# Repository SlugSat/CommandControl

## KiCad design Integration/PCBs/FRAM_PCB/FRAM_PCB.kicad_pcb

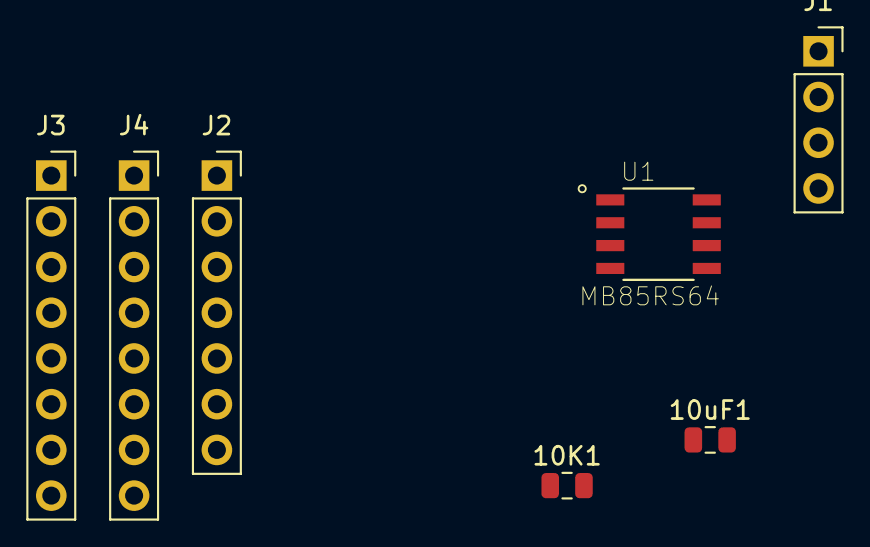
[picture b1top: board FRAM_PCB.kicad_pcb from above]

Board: 2 copper layers, 7 parts (0 on the bottom side), 12 nets, no tracks yet.

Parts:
10K1: R; R_0805_2012Metric
10uF1: C; C_0805_2012Metric
J1: Conn_01x04_Male; PinSocket_1x04_P2.54mm_Vertical
J2: Conn_01x07_Male; PinSocket_1x07_P2.54mm_Vertical
J3, J4: Conn_01x08_Female; PinSocket_1x08_P2.54mm_Vertical
U1: MB85RS64; SOIC127P600X175-8N

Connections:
+5V: 10K1.2, 10uF1.1, J2.6, U1.8
GND: 10uF1.2, J2.7, U1.4
unnamed: 10K1.1, U1.7
unnamed: J1.1, J3.1, J4.1, J4.8
unnamed: J1.2, J3.2, J3.6, J3.7, J3.8, J4.2, J4.6, J4.7
unnamed: J1.3, J3.4, J4.4
unnamed: J1.4, J3.5, J4.5
unnamed: J2.1, U1.2
unnamed: J2.2, U1.5
unnamed: J2.3, U1.6
unnamed: J2.4, U1.3
unnamed: J2.5, U1.1

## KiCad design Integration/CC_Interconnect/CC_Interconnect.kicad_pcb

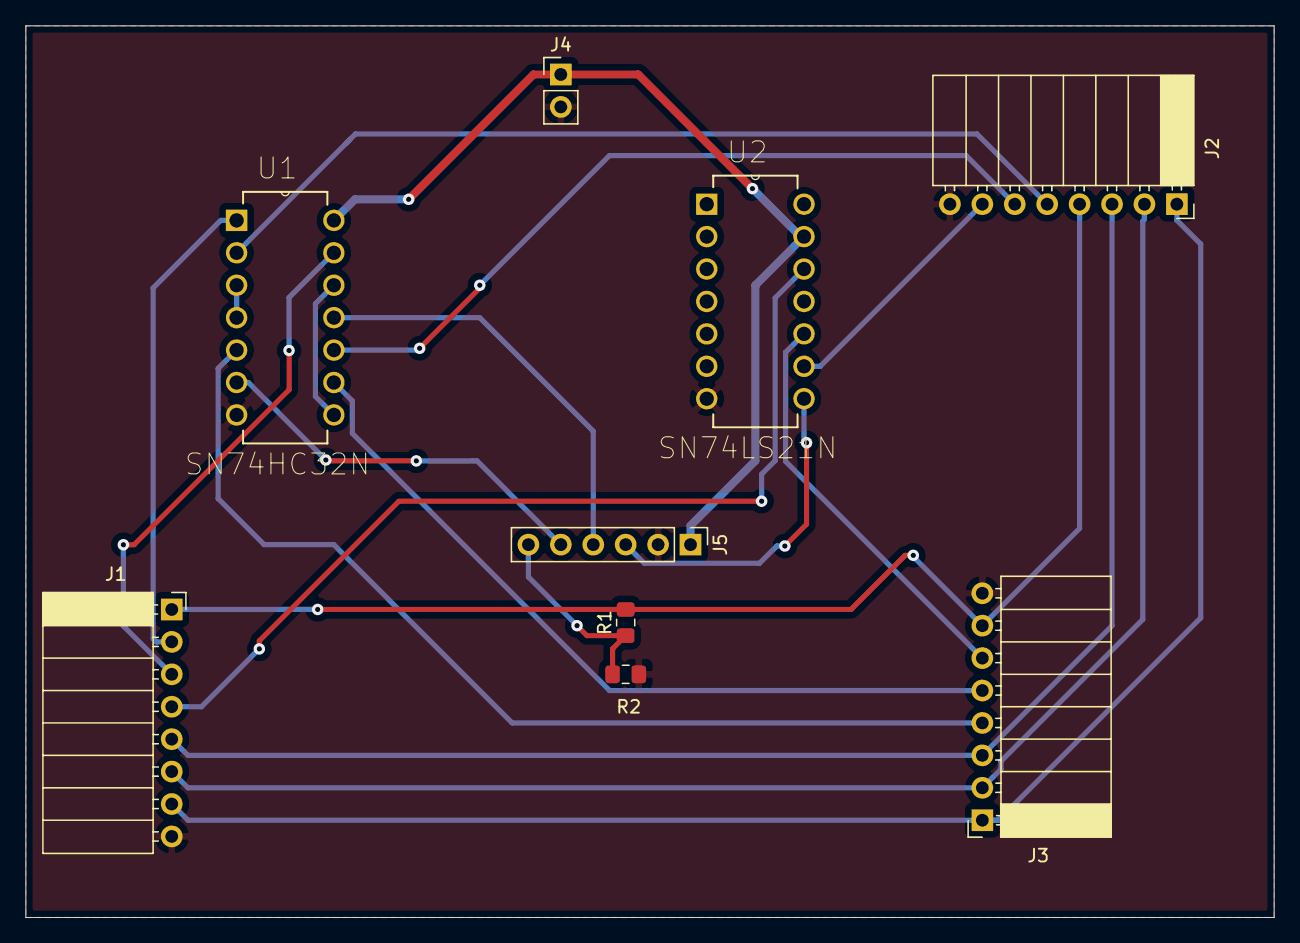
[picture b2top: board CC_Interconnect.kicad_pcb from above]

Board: 2 copper layers, 97.8 x 69.8 mm, 9 parts (0 on the bottom side), 21 nets.

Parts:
J1, J2, J3: Conn_01x08_Male; PinSocket_1x08_P2.54mm_Horizontal
J4: Screw_Terminal_01x02; PinHeader_1x02_P2.54mm_Vertical
J5: Conn_01x06_Male; PinHeader_1x06_P2.54mm_Vertical
R1: 1k; R_0805_2012Metric_Pad1.15x1.40mm_HandSolder
R2: 2K; R_0805_2012Metric_Pad1.15x1.40mm_HandSolder
U1: SN74HC32N; DIP254P762X508-14
U2: SN74LS21N; DIP254P762X508-14

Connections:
+5V: J4.1, J5.1, U1.14, U2.13
GND: J1.8, J2.8, J3.8, J4.2, J5.2, R2.1, U1.7, U2.7
unnamed: J1.1, J2.4, J3.7, R1.2
unnamed: J1.2, U1.1
unnamed: J1.3, U1.13
unnamed: J1.4, U2.12
unnamed: J1.5, J2.3, J3.3
unnamed: J1.6, J2.2, J3.2
unnamed: J1.7, J2.1, J3.1
unnamed: J2.5, U1.2
unnamed: J2.6, U1.10
unnamed: J2.7, U2.9
unnamed: J3.4, U1.5
unnamed: J3.5, U1.9
unnamed: J3.6, U2.10
unnamed: J5.3, U2.8
unnamed: J5.4, U1.11
unnamed: J5.5, U1.6
unnamed: J5.6, R1.1, R2.2
unnamed: U1.3, U1.4
unnamed: U1.8, U1.12

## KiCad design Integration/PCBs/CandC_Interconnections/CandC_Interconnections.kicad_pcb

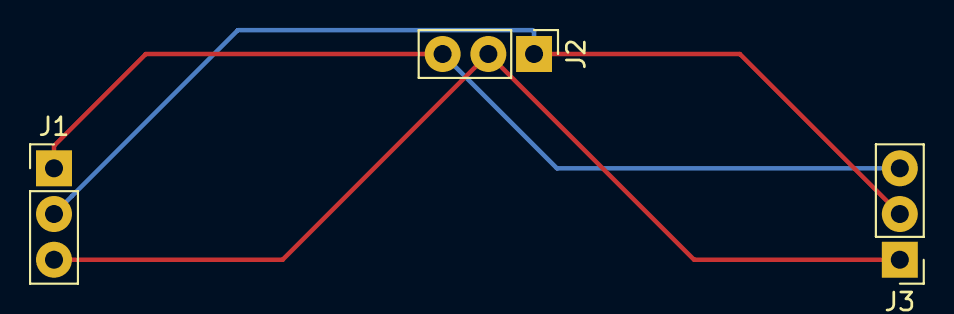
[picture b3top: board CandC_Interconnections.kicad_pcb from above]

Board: 2 copper layers, 3 parts (0 on the bottom side), 3 nets.

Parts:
J1, J2, J3: Conn_01x03_Female; PinHeader_1x03_P2.54mm_Vertical

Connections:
unnamed: J1.1, J2.3, J3.3
unnamed: J1.2, J2.1, J3.2
unnamed: J1.3, J2.2, J3.1

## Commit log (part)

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2019-01-31 Wrote a program that generates a 1kHz PWM signal and changes it's duty cycle 1% every half a second
2019-02-01 Completed PWM interface for mechanical subteam. NEEDS FURTHER DOCUMENTATION
2019-02-02 Created the PSoC5 version of the tester code for the Telemetry board
2019-02-07 added some documentation to PWM_Library and began creating IMU library
2019-02-08 Finished startup and self test functions properly
2019-02-08 Having problems with getting the self test to run
2019-02-11 Implemented a science payload only state and added more documentation
2019-02-11 Updated link to state machine
2019-02-14 Created power modes v2 to implement the new design
2019-02-14 Fixed the States enum in PowerModes.h
2019-02-15 Finished writing each fo the transitions for the power modes state machine
2019-02-15 Added debug print statement functionality
2019-02-15 added more descriptive documentation and added an init function to set up the IMU
2019-02-15 added definitions of methods to get calibration status and check if calibration is done
2019-02-20 Fixed some bugs and made the function names nicer. The state machine now transitions properly
2019-02-20 Added printing out the global variable functionality to help debugging
2019-02-25 fixed the calibration function. Issue was that the system as a whole must be calibrated before the offset registers are set
2019-02-25 added src file for testing
2019-02-25 Added the power modes interrupt test
2019-02-25 Updated the interrupt signal generating test code
2019-03-03 Setup the header file and various values for the telemetry protocol. Next: Write the functions in the .c file and test that they work
2019-03-03 Updated the gitignore for the power executable file
2019-03-04 Filled out each of the functions in protocol.c creating and decoding packets. Now we need to test the various functions
2019-03-05 Updated power modes for testing purposes
2019-03-06 added test for log science command
2019-03-12 Cleaned up first half of test harness and fixed some slight bugs
2019-03-12 Made the test look nice and fixed ACK
2019-03-12 Cleaned up the test harness and made it look nicer
2019-03-14 Made the telemetry test harness look a lot better and added macros to make the code nicer to read
2019-03-14 Fixed a typo in the test code for the telemetry protocol
2019-03-17 working on power mode test
2019-03-17 final debugging of power mode test
2019-03-17 completed testing all functions
2019-03-18 Updated gitignore to match Mechanical's and removed unnecesary files from existing project
2019-03-18 Added basic CC1200 test harness
2019-04-08 added AGC code
2019-04-08 Created the register file to configure the transceiver board
2019-04-08 didn't really change anything but it kinda works now? added DAC waiting thanks to Oly
2019-04-08 Updated the registers list
2019-04-08 Understand how to use SPI to read and write from registers on the CC1200
2019-04-09 added workspace for logic analyzer using waveforms. Also cleaned up pmode transmission side and recieve side to use labeled pins. currently the problem is that the interrupts are not being received p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
2019-04-09 Able to configure registers and read the command strobes
2019-04-10 Setting pins to get the LNA and PA to work
2019-04-10 working on the frontend
2019-04-13 fixed power modes timing diagram test. currently making it more robust as well as adding multiple simulated tests
2019-04-13 added new analog discovery 2 workspace for power modes timing diagram
2019-04-13 Removed unwanted new project
2019-04-13 fixed AD2 workspace for power modes timing diagram
2019-04-15 Some fixes to data tracking issue, still not totally working. Start and End times are not as expected
2019-04-15 Comments
2019-04-17 Fixes to Header Reading
2019-04-17 It mostly works now
2019-04-22 Created code for the imu to read specific sensor data
2019-04-24 RTOS task for AGC started, currently hard faults on UART transmit
2019-04-24 made the error go away by commenting out the printf function, this needs further investigation
2019-04-24 Fixed the SPI functionas and now can accurately read gyro and magnetometer sensor data
2019-04-26 Got the code working again so that we can read and write to all the registers. Now working towards successfully sending packets
2019-04-26 Removed old tests
2019-04-26 Added comments and updated the cod eto make sure that the chip can be talked to. Next: Get the TX buffer to send properly.
2019-04-28 Able to send packets now. Added code to allow this functionality. Next: Test receiving and implement the packets properly
2019-04-28 Added test to check if anything is in the RX fifo, and we got something, it workedgit status! Next: Decode the packets received
2019-04-30 Started the fuel gauge test harness and finished the basic read and write functions
2019-04-30 Setup UART comms
2019-04-30 Able to send blips, this is bad
2019-05-01 Got the fuel gauge to configure registers and read each of the output registers. TO DO: Multiply the multiplier to each of the output register values
2019-05-01 New branch to add FRAM to RTOS
2019-05-01 Ongoing integration of science payload test into RTOS
2019-05-01 Fixed the packet length size problem and able to configure packets of any length and send all data properly. NEXT: Test receiving and decoding packets on the Nucleo
2019-05-02 rewrote the initialize function for the fuel gauge library. followed the software guide closely. Has not been tested yet
2019-05-02 Started a new repository for the integration of the power modes and deleted all files that should not be included with our gitignore
2019-05-02 Added code that will be used to test the power rails. Each rail is powered based on which state you are currently in
2019-05-02 Added gitignore
2019-05-03 Added code to make the TX functionality work at any packet length value
2019-05-03 Added a test that will receive and decode packets. It works successfully. NEXT: Create functions to make the functionality of the telemtry system simpler and then integrate the custom packet protocol
2019-05-03 Separated the functions for the fuel gauge into a new file
2019-05-03 Finished the fuel gauge test harness. Handing off to the power team to test now
2019-05-04 Updated some comments for where the code should be added
2019-05-06 Lack of heap error fixed
2019-05-07 Attempt to get basic communication established - not currently functioning
2019-05-07 Minor updates
2019-05-08 added spi fram
2019-05-08 moved C_C to archives
2019-05-08 Spi_lib_tweak
2019-05-08 Figured out that Union data types can do the conversion very easily between double and uint8_t
2019-05-09 Added a function to go from bytes to a double
2019-05-10 Created a library for date conversions
2019-05-10 Refactored the organization of the packet protocol
2019-05-10 PWM library can now produce 4 PWM signals per timer
2019-05-10 Fixed the packet protocol to become a fixed length. The test.c file tests this new library and confirms that it works
2019-05-10 Deleted Packet_Protocol files so they could be updated to the new fixed length version
2019-05-11 refactored code for SPI FRAM library
2019-05-11 Renamed the packet protocol files
2019-05-11 Added the new FRAM and telemetry libraries to the first integration project
2019-05-11 Fixed dependency in SPI_FRAM.h
2019-05-12 Able to receive in the telemetry integration state machine
2019-05-12 Setup the code so that the telemetry part of the state machine can handle status requests
2019-05-12 Fixed the FRAM libraries
2019-05-12 added spi fram test project
2019-05-12 verified that the refactored SPI FRAM library is working
2019-05-12 Minor updates to printing errors
2019-05-12 Able to read from the SPI Fram and read the latitude and longitude values and send it down to earth
2019-05-13 Able to interface with the I2C fram and send it down to our ground station correctly
2019-05-13 PWM_Test currently calculates RPMs for motor
2019-05-13 The SPI FRAM code is complete so that we can read and write to the FRAM properly
2019-05-13 Finished the last packet handling function. And it works! Next: read real data from the spi fram and log data based on values in the spi fram
2019-05-15 Made some formatting changes
2019-05-15 Everything works except killing myself
2019-05-15 Able to successfully kill myself now
2019-05-15 Added some comments that describe the functionality of the code
2019-05-15 Changed the FRAM library that implements a lock system that will arbitrate control between the microcontrollers
2019-05-17 Added some comments to the power modes blocking out where it commmunicates with the SPI FRAM. Also added the SPI FRAM libraries
2019-05-17 Added the CubeMX pins for the UART and the SPI FRAM
2019-05-17 redid AGC to use MDK and updated AGC to have a range instead of a fixed setpoint
2019-05-17 Updated the spi fram test to work using the arbitration scheme we designed
2019-05-18 Finished adding the peripherals to the power modes
2019-05-18 Added code that can be tested with the power modes in comments at the top of the state machine
2019-05-18 Updated the SPI FRAM library files
2019-05-18 added read and write functions next: find address, init registers
2019-05-19 Added header
2019-05-19 Added Science Temp Monitor
2019-05-19 first version of the code to merge the AGC and power modes
2019-05-20 Temp conversions
2019-05-20 Added other temp types
2019-05-20 Updated the pins in CubeMX
2019-05-21 finished current controller library Next:test it
2019-05-21 Able to load the AGC code to the mcu via the keil project now
2019-05-22 added to the power mode code
2019-05-22 fixed some AGC things to match new pinout
2019-05-22 power and agc compiles now
2019-05-23 correctly calculating RPM using a single hall effect sensor to time a single rotation
2019-05-23 have working code to calculate RPM accurately. now just need to implement actuator library (getSpeed, setSpeed, startMotor)
2019-05-23 first pcb
2019-05-23 Cleaned up the SPI FRAM library and allowed the turning off of the UART debugging
2019-05-23 Created a new project for the F1 board with the FRAM test
2019-05-23 Updated the L1 SPI FRAM test
2019-05-23 Created a new test harness for the fuel gauge using an L1 Micrcontroller
2019-05-23 Current sensor function names refactored
2019-05-23 Changed function names in the fuel gauge library
2019-05-23 Created a library folder for all of the library files
2019-05-24 Started integrating the power modes with the current sensors and fuel gauge
2019-05-24 Updated the power modes code to support the current sensor, voltage rails and fuel gauge
2019-05-24 Removed delay from Get_Lock()
2019-05-24 all pcb files are in integration
2019-05-25 added timer interrupt battery level check
2019-05-25 Deleted an old project file
2019-05-25 passed initial test. next time we test this too we should add in uart stuff so we can print out that we are actually reading correctly
2019-05-25 created test project for low power mode on microcontroller
2019-05-25 low power LED blinker test done, this code can be used elsewhere to replace HAL_Delay with a low power mode
2019-05-25 power in AGC part greatly reduced
2019-05-25 Temp conversion functions
2019-05-27 Finished the power modes. Next: Create functions so that the power modes can be in their separte .c and .h files
2019-05-28 Made the power modesin their own .c and .h files
2019-05-28 Updated PCB design for SPI FRAM Arbitration
2019-05-28 Started the project for the AGC and power modes integrration MCU
2019-05-28 Added an error message when the kill signal is sent
2019-05-28 Added the Low Power Delay test project
2019-05-28 integration for power and AGC works
2019-05-28 renamed folder for AGC + Power integration
2019-05-30 Got the SPI FRAM Arbitration and multiple connection working
2019-05-31 Able to connect the power and science boards together
2019-06-02 removed diode drop from AGC as there is no longer the transistor
2019-06-04 Added interrupts
2019-06-04 Added a timeout in the lock of the FRAM library for the mechanical team
2019-06-04 Updated the main and FRAM code for flatsat board 1
2019-06-04 Updated FRAM code in the telemetry board
2019-06-05 Renamed GPIOA to the built in GPIO Port
2019-06-05 Changed the pin for the reset
2019-06-05 Reorganized the PCB code and updated the SPI FRAM library
2019-06-05 Refactored the science and telemetry board code. It is now 100% flat-sat ready
2019-06-07 Flat-sat tested with mechanical and it works. Made some small optimizations to the science payload code
2019-06-08 Updated GPIO -> User_Label_GPIO_Port
2019-06-11 Fixed the battery level status code
